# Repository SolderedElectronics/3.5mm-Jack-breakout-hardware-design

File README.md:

# 3.5mm Jack breakout Hardware Design

## About the Product

|  |
| :----------------------------------------------------------: |
| [Buy 3.5mm Jack breakout](https://www.solde.red/333088) |

If you are working with audio and need easy access to all the pins of the 3.5mm connector, this breakout makes it possible. It accepts a male 3.5mm connector, in a 4-pin version, and allows access to all connector pins on the header.

---

## Repository Contents

This repository contains all design files for 3.5mm Jack breakout, organized as follows:

- **`CAD` folder**: Contains KiCAD design files, including:
  - Schematics
  - PCB layout
  - Panel PCB layout
  - Source 3D files in Fusion360, if any
  - All files are sorted by version with a detailed change log.
- **`OUTPUTS` folder**: Includes all production-ready files, such as:
  - Bill of Materials (BOM) and interactive BOM (iBOM)
  - PDF versions of schematics
  - 3D `.step` file of the board
  - 3D-printable models
  - Gerber files for PCB manufacturing
  - Image of the pinout of the board
  - Product image
  - Compliance, legal and generic sales documents

Refer to the `Change Log` in the CAD folder for details about updates between versions.

---

## Learn More About the Product

Beyond the repository, explore the following resources:

### Soldered Verify

The **Soldered Verify** system ensures every board you purchase from Soldered is fully functional. It also provides access to exclusive test data for your product. To get started, find the unique Soldered Verify ID on your product's packaging and enter the ID on the [Soldered Verify page](https://soldered.com/verify/) to access test results and additional product details.

### Soldered Community

Soldered Community is your go-to place for technical support. Our engineers track and answer all questions posted there, and it’s a great space for the maker community. Get answers to your questions and solutions for your challenges at [Soldered Community](https://soldered.com/community).

### solde.red

solde.red is an ultimate URL shortener and information hub. Access it by typing solde.red/ followed by your product SKU, e.g., [solde.red/333000](https://solde.red/333000), to find getting-started guides, datasheets, open-source hardware and software files, certifications, images, pinouts, and more. Read more about the shortener [here](https://solde.red/info/).

---

## Contributing

Contributions are welcome! Here’s how you can get involved:

- Submit pull requests to enhance the design or fix issues.
- Report bugs or problems by opening an issue.

We encourage community collaboration to make this product even better.

---

## About Soldered

[Soldered for Makers](https://soldered.com) specializes in designing and manufacturing electronic products tailored for enthusiasts, ranging from hobbyists to professionals. Our portfolio includes electronic boards, sensors, and actuators that are widely utilized in fields such as microelectronics, mechatronics, robotics, programming, and IoT. Every product we offer is designed in-house and built upon open-source hardware and software platforms. Proudly certified and manufactured within the European Union, our catalog likely includes the product you need for your project.

We complement these products with comprehensive tutorials and manuals, product descriptions, schematics, programming codes, and project examples. Our round-the-clock [customer and technical support](https://soldered.com/community) is available for all our products, irrespective of the sales channel. Soldered’s success and services reflect our maker community’s unwavering [trust](https://www.trustpilot.com/review/soldered.com), for which we are deeply grateful. Join our community and create using Soldered products.

---

## License

All Soldered open-source hardware (OSH) is under The TAPR Open Hardware License. Read more in the LICENSE file located in this repository.

**Disclaimer:**

No warranty - all designs in this repository are distributed in the hope that they will be useful, but without any warranty. They are provided "AS IS", therefore without warranty of any kind, either expressed or implied. The entire quality and performance of what you do with the contents of this repository are your responsibility. In no event Soldered Electronics will be liable for your damages, or losses, including any general, special, incidental, or consequential damage arising out of the use or inability to use the contents of this repository. 

---

## Have fun!

Thank you for your support from your fellow makers at Soldered Electronics.

Happy Making!

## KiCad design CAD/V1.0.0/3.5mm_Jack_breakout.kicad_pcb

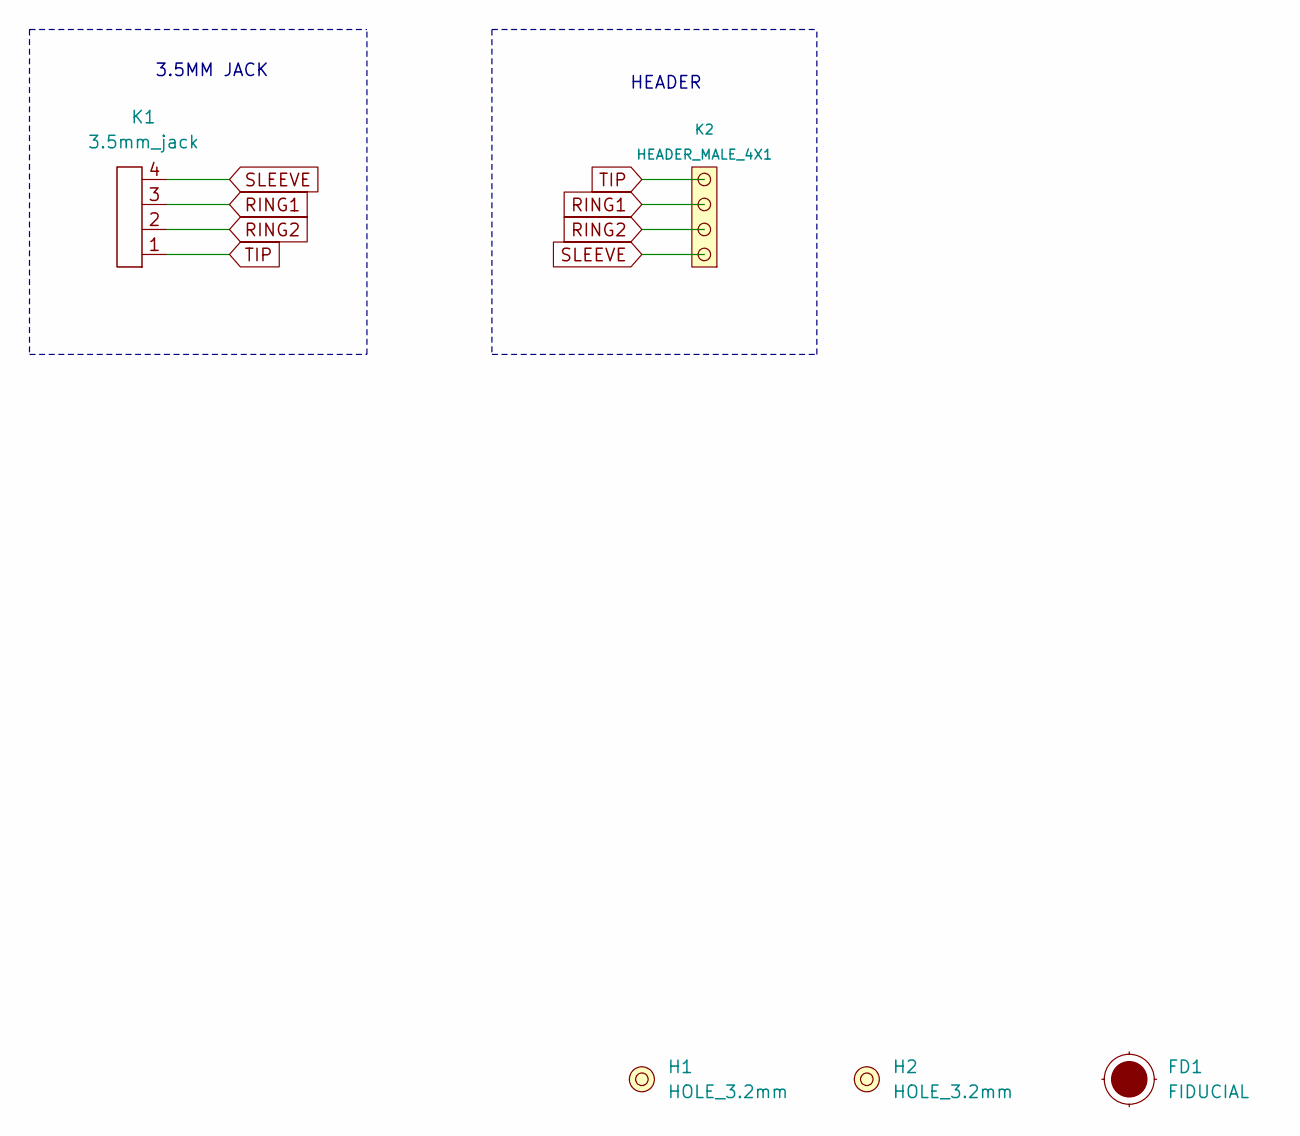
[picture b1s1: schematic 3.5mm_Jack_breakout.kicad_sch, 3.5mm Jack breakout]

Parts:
FD1: FIDUCIAL; FIDUCIAL_23
H1, H2: HOLE_3.2mm
K1: 3.5mm_jack
K2: HEADER_MALE_4X1

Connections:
RING1: K1.3, K2.3
RING2: K1.2, K2.2
SLEEVE: K1.4, K2.1
TIP: K1.1, K2.4

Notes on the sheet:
HEADER
3.5MM JACK

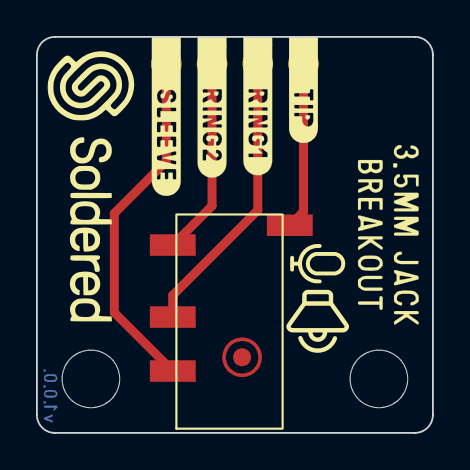
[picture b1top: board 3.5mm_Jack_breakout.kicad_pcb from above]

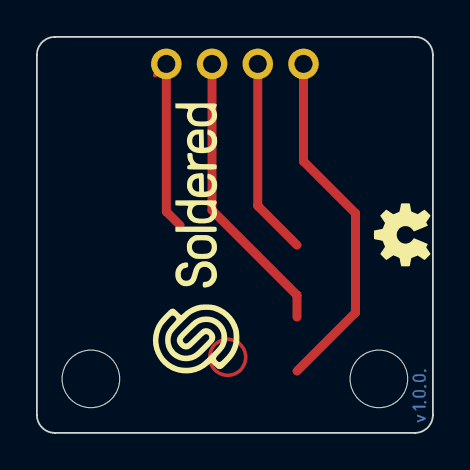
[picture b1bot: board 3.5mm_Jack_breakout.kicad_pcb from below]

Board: 2 copper layers, 22.0 x 22.0 mm, 6 parts (2 on the bottom side), 4 nets.

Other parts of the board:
Ref**: Val**; Version1.0.0.

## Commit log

2022-08-06 Updating open source files.
